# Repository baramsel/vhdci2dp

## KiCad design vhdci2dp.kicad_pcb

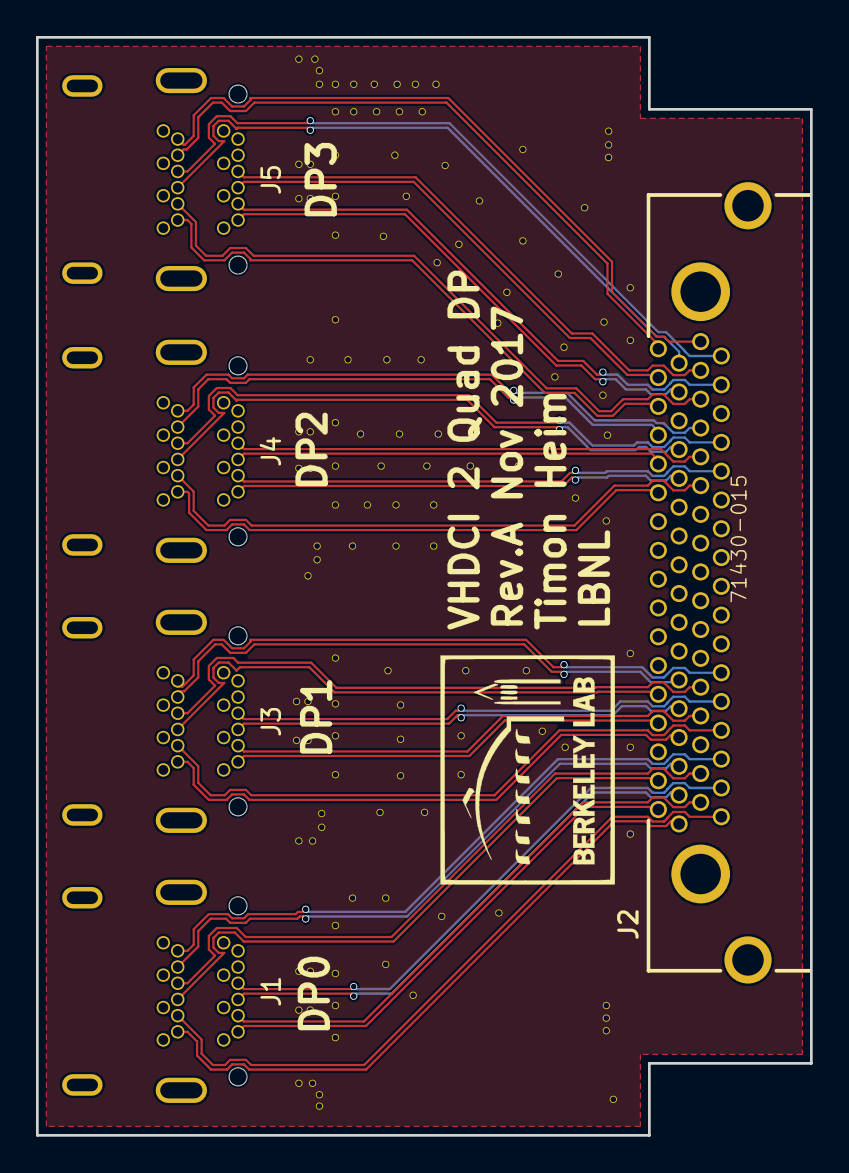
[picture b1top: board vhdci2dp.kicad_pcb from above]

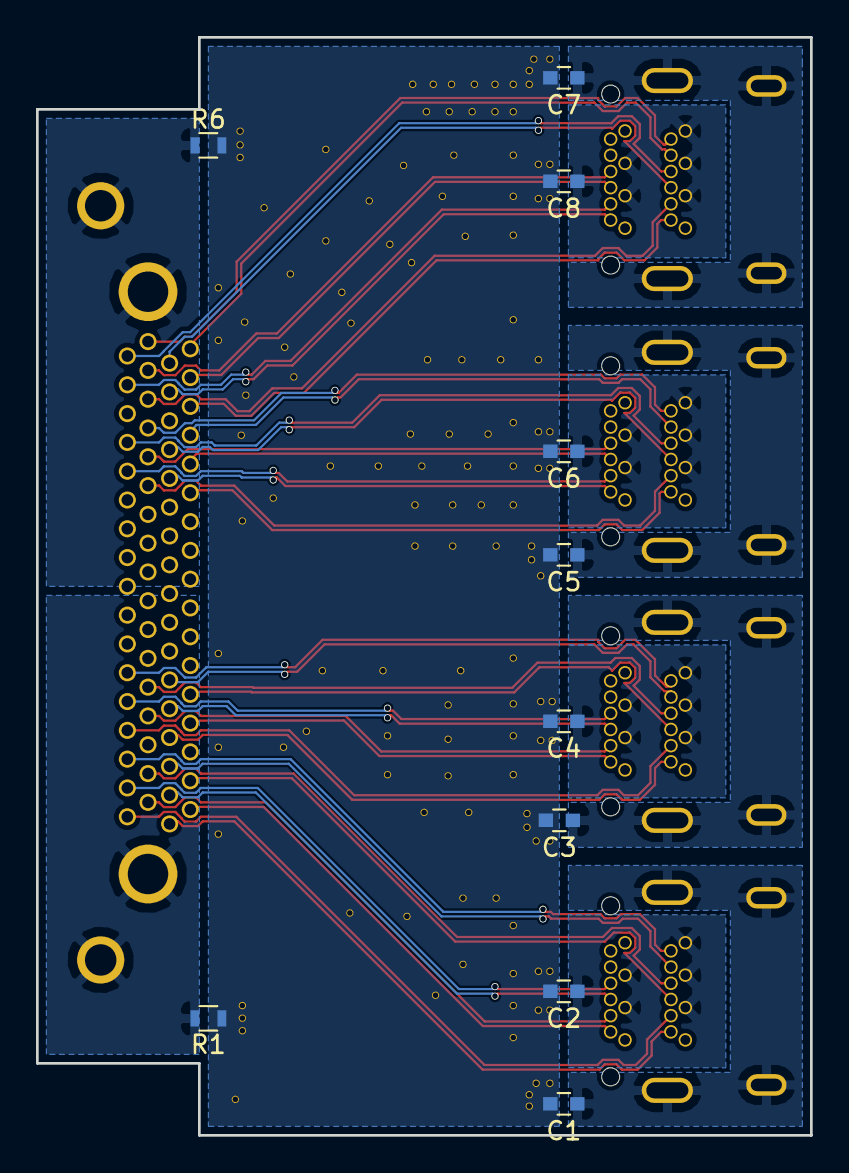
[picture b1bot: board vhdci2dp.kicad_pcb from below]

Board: 4 copper layers, 43.0 x 61.0 mm, 15 parts (10 on the bottom side), 51 nets.

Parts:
C1, C2, C3, C4, C5, C6, C7, C8: C; C_0603
J1, J3, J4, J5: MiniDP
J2: 71430-015; con-molex-vhdci-71430-015
R1, R6: R; R_0603

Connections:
/DP0_GND: C2.1, J1.1, J1.7, J1.8, J1.13, J1.14
/DP0_SHIELD: C1.1, J1.21, J1.22
/DP0_aux_N: J1.18, J2.33
/DP0_aux_P: J1.16, J2.67
/DP0_lane0_N: J1.12, J2.32
/DP0_lane0_P: J1.10, J2.66
/DP0_lane1_N: J1.17, J2.34
/DP0_lane1_P: J1.15, J2.68
/DP0_lane2_N: J1.11, J2.31
/DP0_lane2_P: J1.9, J2.65
/DP0_lane3_N: J1.5, J2.30
/DP0_lane3_P: J1.3, J2.64
/DP1_GND: C4.1, J3.1, J3.7, J3.8, J3.13, J3.14
/DP1_SHIELD: C3.1, J3.21, J3.22
/DP1_aux_N: J2.27, J3.18
/DP1_aux_P: J2.61, J3.16
/DP1_lane0_N: J2.26, J3.12
/DP1_lane0_P: J2.60, J3.10
/DP1_lane1_N: J2.28, J3.17
/DP1_lane1_P: J2.62, J3.15
/DP1_lane2_N: J2.25, J3.11
/DP1_lane2_P: J2.59, J3.9
/DP1_lane3_N: J2.24, J3.5
/DP1_lane3_P: J2.58, J3.3
/DP2_GND: C6.1, J4.1, J4.7, J4.8, J4.13, J4.14
/DP2_SHIELD: C5.1, J4.21, J4.22
/DP2_aux_N: J2.10, J4.18
/DP2_aux_P: J2.44, J4.16
/DP2_lane0_N: J2.9, J4.12
/DP2_lane0_P: J2.43, J4.10
/DP2_lane1_N: J2.11, J4.17
/DP2_lane1_P: J2.45, J4.15
/DP2_lane2_N: J2.8, J4.11
/DP2_lane2_P: J2.42, J4.9
/DP2_lane3_N: J2.7, J4.5
/DP2_lane3_P: J2.41, J4.3
/DP3_GND: C8.1, J5.1, J5.7, J5.8, J5.13, J5.14
/DP3_SHIELD: C7.1, J5.21, J5.22
/DP3_aux_N: J2.4, J5.18
/DP3_aux_P: J2.38, J5.16
/DP3_lane0_N: J2.3, J5.12
/DP3_lane0_P: J2.37, J5.10
/DP3_lane1_N: J2.5, J5.17
/DP3_lane1_P: J2.39, J5.15
/DP3_lane2_N: J2.2, J5.11
/DP3_lane2_P: J2.36, J5.9
/DP3_lane3_N: J2.1, J5.5
/DP3_lane3_P: J2.35, J5.3
GND: C1.2, C2.2, C3.2, C4.2, C5.2, C6.2, C7.2, C8.2, R1.1, R6.2
unnamed: J2.69, R6.1
unnamed: J2.70, R1.2

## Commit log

2017-12-07 revA
